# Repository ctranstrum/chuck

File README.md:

# Charlieflex Keyboard

## Features

- 30-32 key wireless ergo keyboard with aggressive pinky stagger and splay
- central rotary encoder can be used by either hand
- designed for the Seeed Studio [XIAO BLE][xiao] wireless microcontroller
  - also works with the [XIAO RP2040][rp2040] for a lower-cost wired board
- Choc v1 or v2 low profile hotswap switches to allow a wider range of keycap choices
- Unique tiered low-profile "snug sandwich" case with no exposed electrical components
- [RGB LED status][rgbled] visible on the top of the case
- Wireless-first design using [ZMK][zmk] [firmware][firmware] (including [ZMK Studio][studio])
- Internal space (5.5 x 27 x 32 mm) for a "large" 502530 300mAh battery
- [PCB](images/chuck-pcb.jpg) designed with [ergogen][ergogen] for easy modification
- Licensed under the [CERN Open Hardware License v2][ohl]
- All source files available, so you can tweak the design if needed

## Design goals

- Low cost wireless
  - xiao ble is only $10 per controller compared to $25 for the nice!nano
  - Big battery and an option for a dongle, so you can run for months without recharging
  - xiao rp2040 is under $5 with no need to purchase a battery or power switch if you want a wired board
- Ergonomic unibody design for the ultimate comfort and easy portability
  - each half is angled to match the angle of the hands on the board
  - keys are placed where fingers naturally fall, with no excessive stretching
    - 1DFH: no finger has to move farther than 1 key's distance from its home row position
    - when fingers extend, they splay, so the keys also splay outward to follow the fingers
    - the pinky is shorter than the other fingers, so the pinky keys are placed lower to match, and the top pinky key is traded for a ring finger key
    - the inner column of each hand is reduced to two keys to eliminate the need for index finger stretching
    - each thumb gets a single key, with an option for a secondary thumb key if your thumbs are smarter than mine
  - centrally located rotary encoder knob for easy ambidextrous access to scrolling and volume control
  - includes all source files, so if your fingers are slightly different, with a little work you can adjust the keyboard to fit you exactly

- Low profile [3D printable case][case]
  - wireless case is only about 7mm high in front and 15mm high in the back, and comes in three separate pieces, each largely flat on one side for easy FDM printing with minimal fuss
  - for those who don't want or need the extra space required for a battery, a separate wired case is provided, which comes in two pieces and is just under 7mm tall
  - options for 1 or 2 thumb keys on each hand so you can go minimal if desired
  - smaller versions are included for smaller print beds
  - a few different [knobs][case-knob] are included so you can get the height that works best for you
  - bumpons are inset into the case 1mm to minimize their height; they add only 1/2mm in height
- Hotswappable
  - keycaps and switches can be easily removed and exchanged so you can fine-tune the feel
  - ability to move back and forth between or even mix and match choc v1 and choc v2
- Electrostatic mitigation
  - unlike many other ultra-low-profile cases, no electronics are left exposed
  - usb port and power switch are on the back, reset switch is recessed into the bottom of the case

## Build Guide

Interested in building a Charlieflex of your own?
Check out the [Build Guide][guide] for details.

## Ancestry

I designed the [Lintilla keyboard][lintilla] before the Charlieflex,
but over time I realized that I didn't actually like split keyboards with separate halves,
because I move around a bit as I type so I either have to keep adjusting the position
of each half, or I end up contorting my wrists to align with the keyboard.

I also came to the conclusion that I would be better off with fewer pinky keys,
due to the strain of reaching with the pinky, and my thumbs aren't actually
smart enough for three keys each.

However, the basic layout of the remaining keys didn't change much from what
I had before, so if you want a split layout and more keys than the Charlieflex offers,
maybe the [Lintilla][lintilla] is for you.

## Descendants

I found some issues with running a charlieplex matrix on a wireless board where
battery levels can impact the performance of the diodes, which need very precise
cutoffs to interpret the keys being pressed; it made some of my 3-key combos a little
unreliable in practice.

So I went back to the drawing board and discovered an extra two usable pins on the xiao ble.
Using those allowed me to build the [Patagona gigas][patagona], with 32 keys and a five-way switch,
along with the [Patagona chaski][patagona], with 42 keys,
the same number of keys used by the [Lintilla][lintilla].

## Builds

My Charlieflex, in the Twentyone Chuck Street layout, with 2 keys for the left thumb and one key for the right.
I'm using [Lofree Hades Choc v2 switches][hades]
and [Nuphy Shiokaze nSA keycaps][shiokaze].

---

I also built a pink Charlieflex for the office,
this time with [LDSA keycaps][ldsa]
on [Bokeh Ambient Choc v1 switches][bokeh].

---

An alternate snap-fit case that uses fewer screws and is a bit more stable
if you tend to use the keyboard directly on your lap.

[ergogen]: https://ergogen.xyz
[bokeh]: https://lowprokb.ca/products/ambients-silent-choc-switches?variant=51042310062244
[case]: cases#readme
[case-knob]: cases#encoder-knobs
[firmware]: https://github.com/ctranstrum/chuck/tree/zmk
[guide]: BUILD.md
[hades]: https://www.lofree.co/products/hades-low-profile-pom-switches
[ldsa]: https://lowprokb.ca/collections/keycaps/products/ldsa-low-profile-blank-keycaps
[lintilla]: https://github.com/ctranstrum/lintilla
[ohl]: LICENSE.txt
[patagona]: https://github.com/ctranstrum/patagona
[rgbled]: https://github.com/caksoylar/zmk-rgbled-widget
[rp2040]: https://www.seeedstudio.com/XIAO-RP2040-v1-0-p-5026.html
[shiokaze]: https://nuphy.com/collections/keycaps/products/shiokaze-nsa-dye-sub-pbt-keycaps
[studio]: https://zmk.dev/docs/features/studio
[twilight]: https://lowprokb.ca/products/ambients-silent-choc-switches?variant=44873426436260
[xiao]: https://wiki.seeedstudio.com/XIAO_BLE/
[zmk]: https://zmk.dev

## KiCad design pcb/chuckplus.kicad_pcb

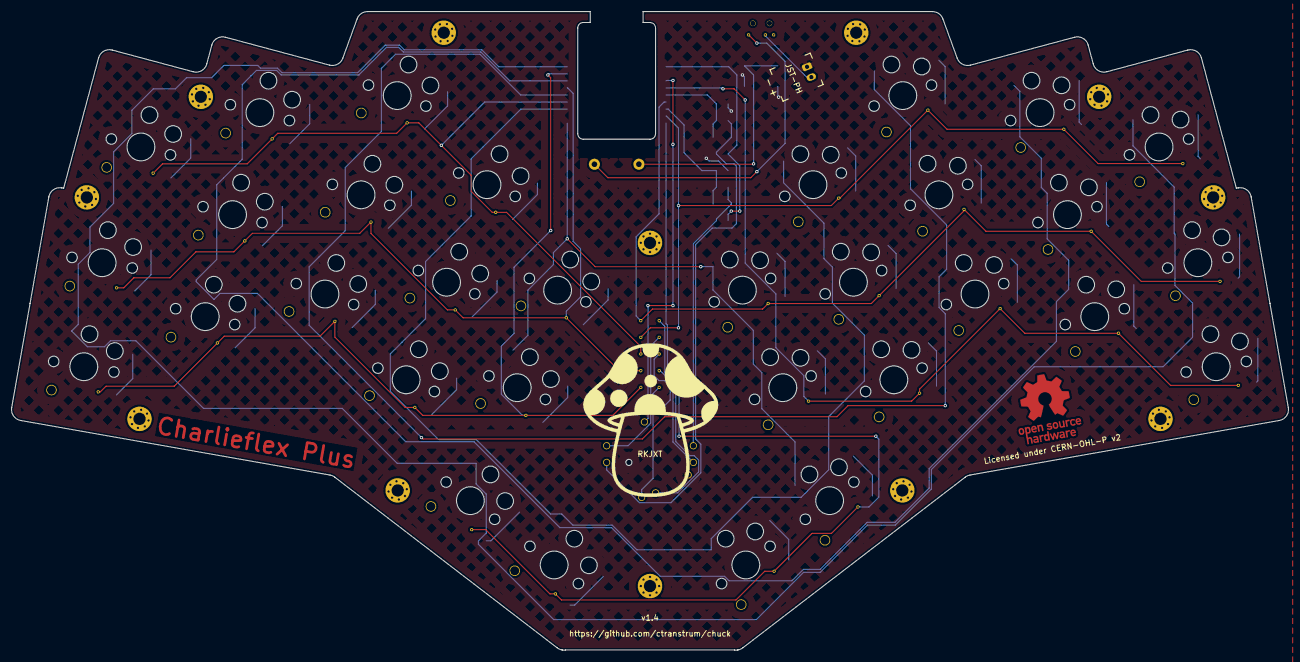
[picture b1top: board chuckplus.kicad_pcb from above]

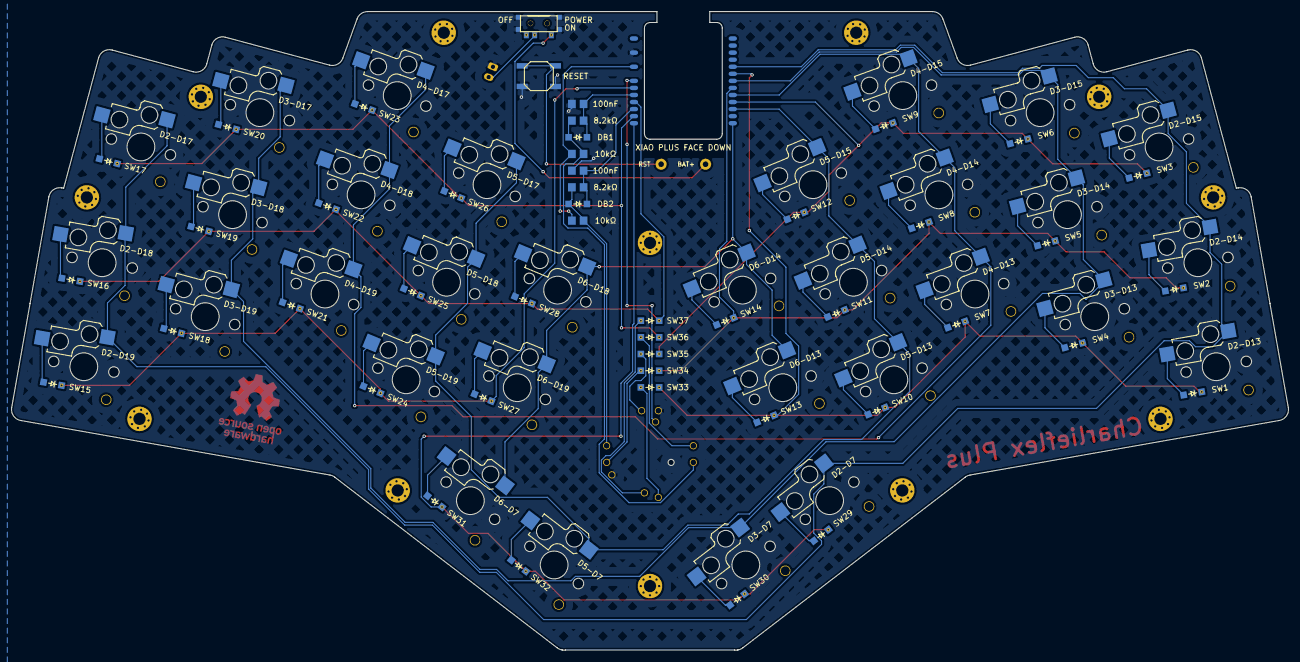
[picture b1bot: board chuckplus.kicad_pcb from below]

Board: 2 copper layers, 229.7 x 114.9 mm, 83 parts (78 on the bottom side), 58 nets.

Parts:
DB1, DB2, DB3, DB4, DB5, DB6: Smd0805
DB7, DB8: ComboDiode
ENC1: Alps_Alpine_RKJXT
JST1: battery_connector_jst_ph_2
PAD1, PAD2: SMDPad
S1, S2, S3, S4, S5, S6, S7, S8, S9, S10, S11, S12, S13, S14, S15, S16, S17, S18, S19, S20, S21, S22, S23, S24, S25, S26, S27, S28, S29, S30, S31, S32: switch_choc_v1_v2
SW1, SW2, SW3, SW4, SW5, SW6, SW7, SW8, SW9, SW10, SW11, SW12, SW13, SW14, SW15, SW16, SW17, SW18, SW19, SW20, SW21, SW22, SW23, SW24, SW25, SW26, SW27, SW28, SW29, SW30, SW31, SW32, SW33, SW34, SW35, SW36, SW37: ComboDiode
SW38: pts526
T1: SPDT_C128955

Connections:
A_DB: DB1.1, DB2.1, DB7.1
BAT+: PAD1.1, T1.1
B_DB: DB4.1, DB5.1, DB8.1
D2: S1.1, S2.1, S3.1, S15.1, S16.1, S17.1, S29.1
D3: S4.1, S5.1, S6.1, S18.1, S19.1, S20.1, S30.1
D4: S7.1, S8.1, S9.1, S21.1, S22.1, S23.1
D5: S10.1, S11.1, S12.1, S24.1, S25.1, S26.1, S32.1
D6: S13.1, S14.1, S27.1, S28.1, S31.1
D7: SW29.1, SW30.1, SW31.1, SW32.1
D13: SW1.1, SW4.1, SW7.1, SW10.1, SW13.1, SW33.1
D14: SW2.1, SW5.1, SW8.1, SW11.1, SW14.1, SW34.1
D15: SW3.1, SW6.1, SW9.1, SW12.1, SW35.1
D17: SW17.1, SW20.1, SW23.1, SW26.1, SW36.1
D18: SW16.1, SW19.1, SW22.1, SW25.1, SW28.1, SW37.1
D19: SW15.1, SW18.1, SW21.1, SW24.1, SW27.1
ENC_A: DB2.2, DB3.1, DB7.2, ENC1.ENC_A
ENC_B: DB5.2, DB6.1, DB8.2, ENC1.ENC_B
GND: DB1.2, DB4.2, ENC1.ENC_COM, ENC1.GND, JST1.1, SW38.1
RAW: JST1.2, T1.2
RST: PAD2.1, SW38.2
VCC: DB3.2, DB6.2
index_bottom: S10.2, SW10.2
index_home: S11.2, SW11.2
index_top: S12.2, SW12.2
inner_bottom: S13.2, SW13.2
inner_home: S14.2, SW14.2
inner_spot: S29.2, SW29.2
middle_bottom: S7.2, SW7.2
middle_home: S8.2, SW8.2
middle_top: S9.2, SW9.2
mirror_index_bottom: S24.2, SW24.2
mirror_index_home: S25.2, SW25.2
mirror_index_top: S26.2, SW26.2
mirror_inner_bottom: S27.2, SW27.2
mirror_inner_home: S28.2, SW28.2
mirror_inner_spot: S31.2, SW31.2
mirror_middle_bottom: S21.2, SW21.2
mirror_middle_home: S22.2, SW22.2
mirror_middle_top: S23.2, SW23.2
mirror_outer_spot: S32.2, SW32.2
mirror_pinky_bottom: S15.2, SW15.2
mirror_pinky_home: S16.2, SW16.2
mirror_pinky_top: S17.2, SW17.2
mirror_ring_bottom: S18.2, SW18.2
mirror_ring_home: S19.2, SW19.2
mirror_ring_top: S20.2, SW20.2
outer_spot: S30.2, SW30.2
pinky_bottom: S1.2, SW1.2
pinky_home: S2.2, SW2.2
pinky_top: S3.2, SW3.2
ring_bottom: S4.2, SW4.2
ring_home: S5.2, SW5.2
ring_top: S6.2, SW6.2
rkjxt_A: ENC1.A, SW33.2
rkjxt_B: ENC1.B, SW34.2
rkjxt_C: ENC1.C, SW35.2
rkjxt_D: ENC1.D, SW36.2
rkjxt_PUSH: ENC1.PUSH, SW37.2

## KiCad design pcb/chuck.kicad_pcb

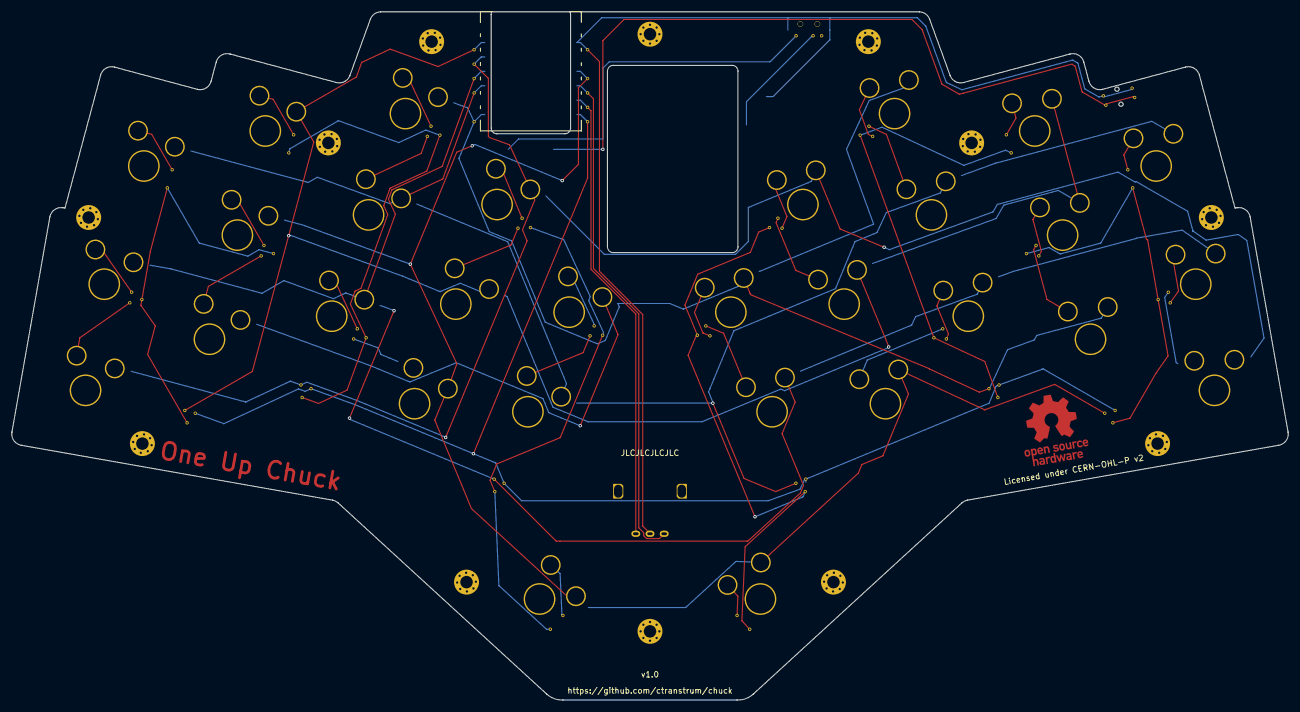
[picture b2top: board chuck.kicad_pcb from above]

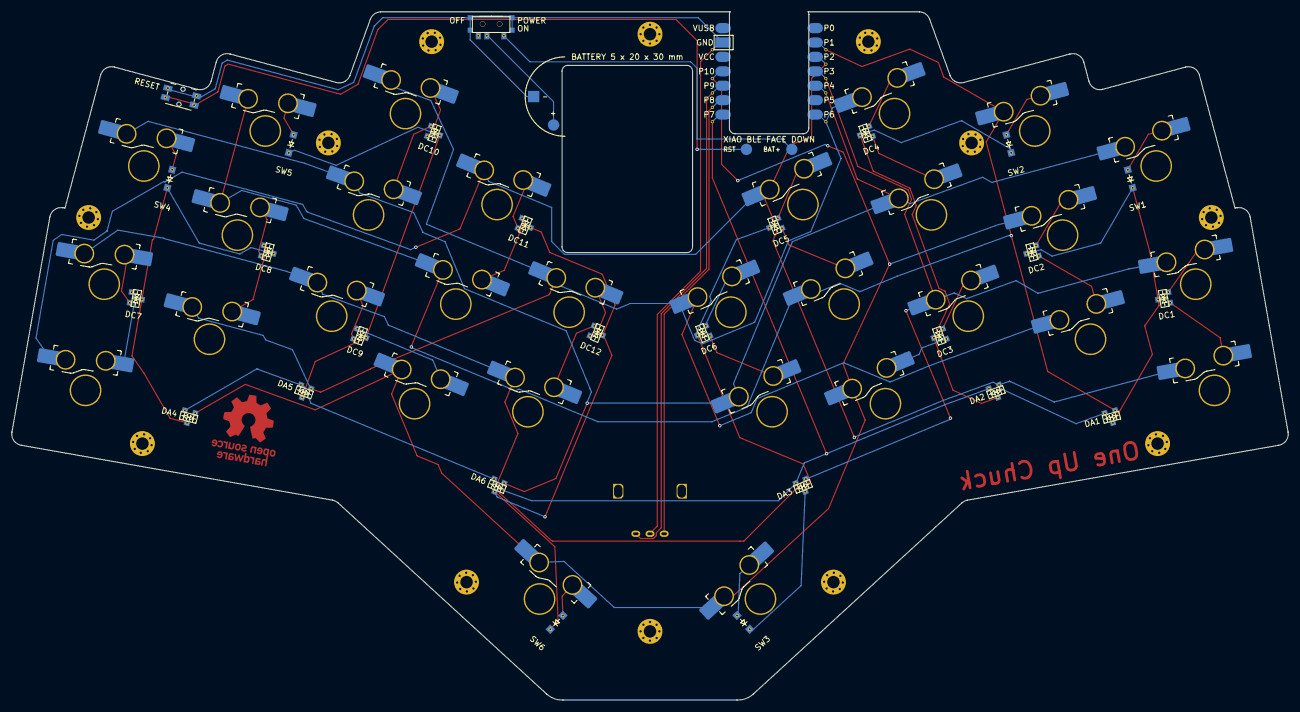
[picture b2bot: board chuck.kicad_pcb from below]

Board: 2 copper layers, 225.0 x 121.3 mm, 63 parts (54 on the bottom side), 49 nets.

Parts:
ARC1: arc_guide
B1: Panasonic_EVQPUL_EVQPUC
DA1, DA2, DA3, DA4, DA5, DA6: ComboDiode
DC1, DC2, DC3, DC4, DC5, DC6, DC7, DC8, DC9, DC10, DC11, DC12: ComboDiode
ENC1: rotary_encoder_ec11_ec12
MCU1: xiao-ble
PAD1, PAD2, PAD3, PAD4: SMDPad
S1, S2, S3, S4, S5, S6, S7, S8, S9, S10, S11, S12, S13, S14, S15, S16, S17, S18, S19, S20, S21, S22, S23, S24, S25, S26, S27, S28, S29, S30: switch_gateron_ks27_ks33
SW1, SW2, SW3, SW4, SW5, SW6: ComboDiode
T1: SPDT_C128955

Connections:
BAT+: PAD1.1, T1.1
CP0: DA1.2, MCU1.2, MCU1.16, S6.1, S11.1, S19.1, S20.1, S25.1
CP1: DA2.2, MCU1.3, MCU1.17, S1.1, S12.1, S15.1, S26.1
CP2: DA3.2, MCU1.4, MCU1.18, S2.1, S7.1, S16.1, S21.1, S27.1
CP3: DA6.2, MCU1.5, MCU1.19, S3.1, S8.1, S13.1, S17.1, S22.1
CP4: DA5.2, MCU1.7, MCU1.20, S4.1, S9.1, S14.1, S18.1, S23.1, S28.1
CP5: DA4.2, MCU1.11, MCU1.24, S5.1, S10.1, S24.1, S29.1, S30.1
CP_INT: DA1.1, DA2.1, DA3.1, DA4.1, DA5.1, DA6.1, MCU1.8, MCU1.27
D_CP0: DA1.3, DC1.3, DC2.3, SW1.1
D_CP1: DA2.3, DC3.3, DC4.3, SW2.1
D_CP2: DA3.3, DC5.3, DC6.3, SW3.1
D_CP3: DA6.3, DC11.3, DC12.3, SW6.1
D_CP4: DA5.3, DC9.3, DC10.3, SW5.1
D_CP5: DA4.3, DC7.3, DC8.3, SW4.1
ENC_A: ENC1.A, MCU1.10, MCU1.25
ENC_B: ENC1.B, MCU1.9, MCU1.26
GND: B1.1, ENC1.C, MCU1.13, MCU1.22, PAD4.1
RAW: PAD3.1, T1.2
RST: B1.2, PAD2.1
index_bottom: DC3.2, S10.2
index_home: DC5.2, S11.2
index_top: DC5.1, S12.2
inner_bottom: DC6.2, S13.2
inner_home: DC6.1, S14.2
middle_bottom: DC3.1, S7.2
middle_home: DC4.2, S8.2
middle_top: DC4.1, S9.2
mirror_index_bottom: DC9.2, S24.2
mirror_index_home: DC11.2, S25.2
mirror_index_top: DC11.1, S26.2
mirror_inner_bottom: DC12.2, S27.2
mirror_inner_home: DC12.1, S28.2
mirror_middle_bottom: DC9.1, S21.2
mirror_middle_home: DC10.2, S22.2
mirror_middle_top: DC10.1, S23.2
mirror_pinky_bottom: DC7.2, S15.2
mirror_pinky_home: DC7.1, S16.2
mirror_pinky_top: S17.2, SW4.2
mirror_ring_bottom: DC8.2, S18.2
mirror_ring_home: DC8.1, S19.2
mirror_ring_top: S20.2, SW5.2
mirror_thumb_spot: S30.2, SW6.2
pinky_bottom: DC1.2, S1.2
pinky_home: DC1.1, S2.2
pinky_top: S3.2, SW1.2
ring_bottom: DC2.2, S4.2
ring_home: DC2.1, S5.2
ring_top: S6.2, SW2.2
thumb_spot: S29.2, SW3.2

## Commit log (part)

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2024-12-24 Ready for first prototype
2024-12-24 Added ground fill
2024-12-24 Gerber file ready
2024-12-24 Added bill of materials
2024-12-24 fix image
2024-12-24 fix link
2024-12-24 choice of xiao boards
2024-12-29 update info on bourns encoders for wireless builds
2024-12-31 begin work on the case
2025-01-02 add cases
2025-01-03 update encoder cutouts in bottom case
2025-01-10 first run at a One Up Chuck firmware
2025-01-10 update layout and dongle information
2025-01-10 move encoder line to correct spot in file
2025-01-10 Add images folder
2025-01-10 fix flash layer keymap
2025-01-10 fix spelling error
2025-01-10 keymap drawer is not working?
2025-01-10 keymap-drawer render
2025-01-10 fix layout for keymap drawer
2025-01-10 fix bt keys
2025-01-10 try different keymap drawer parameters
2025-01-10 Add keymap drawer config
2025-01-10 maybe move dts to the draw stage
2025-01-10 keymap drawer updates
2025-01-10 keymap image
2025-01-10 adjust combos
2025-01-10 keymap image updates
2025-01-10 add a few keymap icons
2025-01-10 add combo for tab
2025-01-10 sticky shift label
2025-01-14 update PCB to v1.1, using correct diodes
2025-01-14 enable dongle in conf
2025-01-14 add rgbled status keys
2025-01-15 four steps per trigger
2025-01-15 three steps per trigger?
2025-01-15 80/20 rule
2025-01-15 add tab to nav layer for Cmd-Tab, arrows
2025-01-15 wow, I think it really is 3 steps per trigger
2025-01-15 changing the order of building the case fixes the crazy geometry for some reason
2025-01-15 small build guide changes, still pending an official build
2025-01-16 update default firmware
2025-01-16 update firmware instructions
2025-01-16 try to get mouse scrolling to work
2025-01-16 mouse scroll fix
2025-01-16 mouse scroll input processor
2025-01-16 why is this not working
2025-01-16 rolling back ineffective scroll fixes
2025-01-17 try a keymap binding for scroll, just to test
2025-01-17 increase tap duration for mouse scroll encoder rotation events
2025-01-17 scrolling works, but is way too fast now
2025-01-17 zero in on the scroll speed
2025-01-17 getting closer to correct scroll speed
2025-01-17 slow the encoder mouse scroll speed a bit
2025-01-17 try a custom y scroll movement
2025-01-17 adjust encoder mouse scrolling
2025-01-19 add knob and dovetail top case
2025-01-19 add note for ergogen-generated stl files
2025-01-19 add a little more detail to the READM
2025-01-22 add a little more detail to the README
2025-01-23 add globe key
2025-02-04 v1.2 of the board
2025-02-04 add the gerbers
2025-02-04 add ec11 and rp2040
2025-02-04 fix a few errors
2025-02-04 fix keymap drawer
2025-02-04 remove wakeup-source
2025-02-04 optimize the composite driver by using blanks in the chuck mapping
2025-02-04 fix stupid spelling mistake
2025-02-04 increase depth of bumpon cavity
2025-02-05 add space in the bottom case for the encoder switch pins
2025-02-05 use encoder button for media controls
2025-02-05 fix encoder
2025-02-06 update keymap
2025-02-06 update codes for keymap drawer
2025-02-06 fix syntax error in yaml
2025-02-06 fix syntax in yaml
2025-02-06 draw combos
2025-02-06 update combo depictions
2025-02-06 keymap drawing refinements
2025-02-06 more precise keymap explanations
2025-02-08 try a new rgbled widget
2025-02-09 add rgbled widget back to rp2040 builds
2025-02-09 try latest version of rgbled widget
2025-02-09 oh, I can re-run the job on gitlab's website
2025-02-09 test the layer change option
2025-02-09 remove layer change option
2025-02-10 more experimentation on scroll amount
2025-02-10 small scrolls barely move the needle, try holding longer?
2025-02-11 weird that 50ms seems not to work at all
2025-02-11 test build assert failure
2025-02-11 revert failure test
2025-02-12 try different scroll settings
2025-02-12 double the scrolling rate
2025-02-14 move modifiers out from under arrow keys
2025-02-14 fix syntax error
2025-02-17 swap num/nav layers
2025-02-18 layer color changes accepted into rgbled widget
2025-02-19 update layer colors
2025-02-19 the recommended encoder has four steps per trigger
2025-02-20 revert num/nav swap
2025-02-20 wakeup source in composite kscan
2025-02-20 add mouse scroll combos
2025-02-20 add explanation of home row mods
2025-02-21 still working on that scroll
2025-02-21 key scroll is better, but that rotary scroll
2025-02-26 try different scroll settings for keypress vs rotary encoder
2025-02-26 use the correct code
2025-02-26 use the move code
2025-02-27 experiment with longer time-to-max-speed settings
2025-02-27 add photo
2025-02-27 add info about the RP2040
2025-02-27 revert to built-in scroll settings
2025-02-27 add a note to the build guide about v1.2 being usable
2025-03-01 reduce the rotary scroll speed a bit
2025-03-11 PCB for v1.3 is sent off to be manufactured
2025-03-11 update info for v1.3 of the board
2025-03-28 a few more updates for v1.3
2025-03-28 minor edits
2025-04-01 Spelling
2025-04-02 firmware for charlieflex v1.3
2025-04-02 select a default physical layout
2025-04-02 update keyboard name
2025-04-02 syntax error
2025-04-02 update transforms
2025-04-02 name file correctly
2025-04-02 update keymap drawer
2025-04-02 update draw action
2025-04-02 explain new keymap
2025-04-02 use combos for mouse move, not arrow keys
2025-04-02 add keymap example for the One Up Chuck layout
2025-04-02 set the layout for the One Up Chuck board
2025-04-02 draw when the workflow is updated
2025-04-03 try to draw the one up chuck keymap
2025-04-07 update cases models for v1.3 of the board
2025-04-07 missed attic screws on bottom case
2025-04-09 update information on battery
2025-04-11 add case options for different number of thumb keys
2025-04-11 add printing hints
2025-04-11 add printing hints for encoder knobs as well
2025-04-12 add additional case / build information
2025-04-15 right click
2025-04-22 fix sticky shift to be quick release
2025-04-22 add required parameters
2025-04-22 add keybd layer to outer key
2025-04-22 add studio unlock combo
2025-04-30 Write the build guide
2025-04-30 Add a note about featured keyboards
2025-04-30 build guide fixes
2025-04-30 Add missing image
2025-05-01 update readme and build guide
2025-05-01 Add sample photo of a completed Charlieflex
2025-05-01 exlain 1dfh principles
2025-05-10 add image of charlieflex with chocv2
2025-05-13 update bom
2025-05-13 add labeled image of the xiao RST pad
2025-06-13 update error image
2025-06-26 design case specifically for a wired build
2025-06-26 add xiao rp2040 reset pad diagram
2025-07-03 Additional notes for a wired build
2025-07-03 Fix a few additional details
2025-07-03 pin to zmk v0.2
2025-07-03 increase default debounce in config
2025-07-15 showcase the pink Charlieflex
2025-07-15 add more troubleshooting notes
2025-07-15 typo
2025-07-15 show default keymap base layer
2025-07-15 add keymap base layer image
2025-07-22 fix conf file name
2025-08-22 add two-finger combos for esc tab bspc ret
2025-08-22 limit bspc and ret combos to base and num layers
2025-09-12 reorder combos for better keymap image generation
2025-09-12 drop pinky tab and ret combos to bottom row
2025-09-12 update keymap to show combos
2025-09-12 fix link to cases
2025-10-14 testing a block case
2025-10-14 fix typo
2025-10-23 look at a snap fit case option
2025-10-24 test a snap-fit type case
2025-10-26 Finalize the snap-fit case
2025-11-11 Rectangle case photos
2025-11-11 more case pictures
2025-11-11 full size case sample photos
2025-11-11 photo of bumpons
2025-11-11 add finger map
2025-11-11 better phrasing
2025-11-11 better order for cases presentation
2025-11-11 add caveats
2025-11-11 use an svg for finger placement
2025-11-11 update svg
2025-11-11 better centering
2026-02-20 add require-prior-idle-ms to a few combos on commonly typed keypairs
2026-02-20 pin version
2026-02-25 initial work on the chuck plus
2026-03-02 charlieflex plus board
2026-03-03 v1.4 of the board for xiao nrf52840 plus
2026-03-17 add chuck plus zmk
2026-03-18 update the README
2026-03-23 chuck plus with rkjxt encoder
2026-04-08 v4 with xiao nrf52840 plus, rkjxt and hardware debounce
2026-04-08 add knob for rkjxt
2026-04-15 update stl files
2026-04-21 update chuck plus firmware
2026-04-21 fix kscan
2026-04-22 begin change for joystick combos
2026-04-23 move joystick keys to bottom
2026-04-23 update keymap drawer to draw chuck plus
2026-04-23 finalize joystick changes
2026-04-23 fix keymap drawer for chuckplus
2026-04-24 add config for chuck plus
2026-04-24 encoder rotation multipliers
2026-04-24 update chuck plus keymap config
2026-04-25 Reverse A and B encoder pins to get the correct clockwise rotation
2026-04-25 increase require-prior-idle-ms settings
2026-04-27 fix keymap svg
2026-04-27 adjust knob location
2026-04-27 add side screws to the rectangle case
2026-05-01 update cases
2026-05-04 mute key for keymap drawer
2026-05-04 update features

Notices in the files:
pcb/chuck.kicad_pcb:
Licensed under CERN-OHL-P v2
